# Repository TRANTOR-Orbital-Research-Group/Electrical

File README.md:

View this project on [CADLAB.io](https://cadlab.io/project/30550). 

# Electrical

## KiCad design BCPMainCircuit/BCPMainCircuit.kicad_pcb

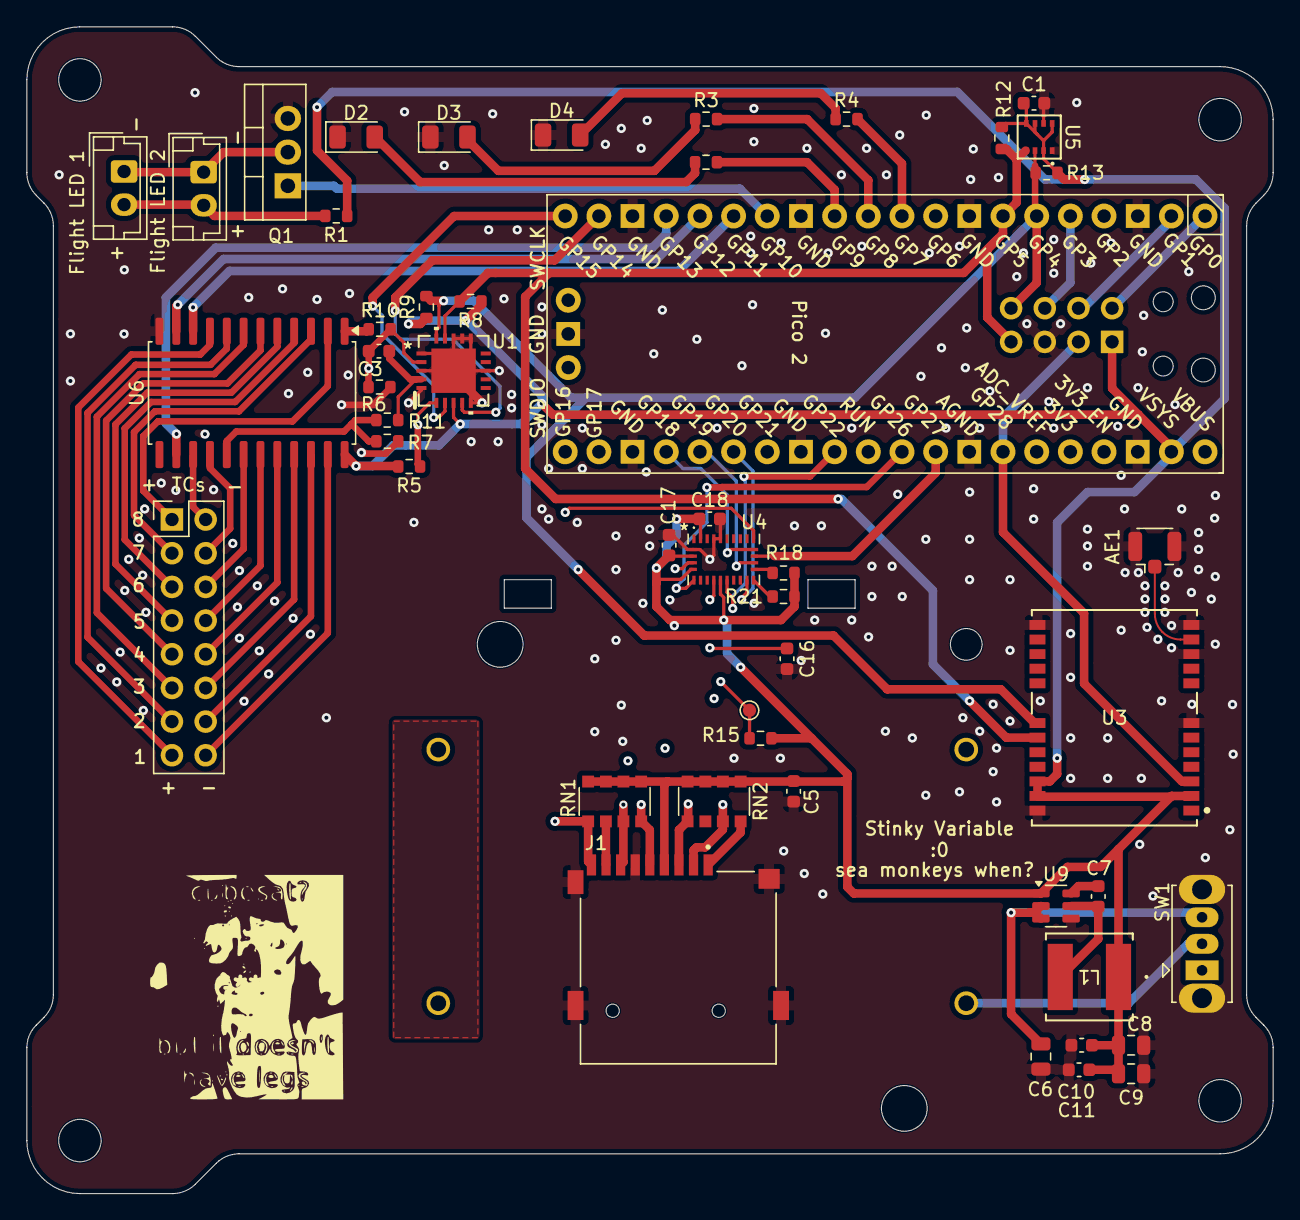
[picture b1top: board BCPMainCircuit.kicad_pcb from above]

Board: 4 copper layers, 94.0 x 88.0 mm, 49 parts (1 on the bottom side), 60 nets.

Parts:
AE1: Antenna_Shield; U.FL_Hirose_U.FL-R-SMT-1_Vertical
BT1: 1097P; BAT_1097P
C1: 220nf; C_0603_1608Metric
C3, C16, C17, C18: 0u1f; C_0603_1608Metric
C5, C11: 1uF; C_0603_1608Metric
C6: 10uF; C_0805_2012Metric
C7: 0u1F; C_0603_1608Metric
C8, C9: 22uF; C_0805_2012Metric
C10: 4u7F; C_0603_1608Metric
D1: Flight LED 1; JST_EH_B2B-EH-A_1x02_P2.50mm_Vertical
D2: DEBUG 1; LED_1206_3216Metric
D3: DEBUG 2; LED_1206_3216Metric
D4: BEBUG 3; LED_1206_3216Metric
D5: Flight LED 2; JST_EH_B2B-EH-A_1x02_P2.50mm_Vertical
J1: MSD-4-A; CUI_MSD-4-A
L1: 4u7H; IND_VLS6045EX-4R7M_TDK
Q1: IRLB8721PBF; TO-220-3_Vertical
R1: 20Ω; R_0603_1608Metric
R2, R3, R4: 65Ω; R_0603_1608Metric
R5: 1M; R_0603_1608Metric
R6, R7: 2M; R_0603_1608Metric
R8, R9: 10k; R_0603_1608Metric
R10, R11: 100; R_0603_1608Metric
R12, R13: 4.7kΩ; R_0603_1608Metric
R15: 10kΩ; R_0603_1608Metric
R18, R21: 4kΩ; R_0603_1608Metric
RN1, RN2: CAY16-4702F4LF; R_Array_Convex_4x1206
SW1: Switch; SW_Slide_SPDT_Straight_CK_OS102011MS2Q
TCs: PinHeader_2x08_P2.54mm_Vertical
U1: MCP9601T-E/MX; MQFN20_NU_MCH
U2: Pico 2; RPi_Pico_SMD_TH
U3: NEO-M9N-00B; SMT_9N-00B_UBL
U4: BNO085; IC_BNO085
U5: BME280; BME280(1)
U6: CD4097B; SOIC-24W_7.5x15.4mm_P1.27mm
U9: AP63203WU-7; TSOT-23-6

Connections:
+3.3V: C1.1, C5.1, C8.1, C9.1, C10.1, C11.1, C17.1, C18.1, J1.4 (VDD), L1.1, R1.1, R5.2, R8.1, R9.1, R12.1, R13.2, R15.1, R18.2, R21.2, RN1.1, RN1.2, RN1.3, RN1.4, RN2.1, RN2.2, RN2.3, RN2.4, U1.8 (VDD), U2.39 (VSYS), U3.2 (D_SEL), U3.22 (V_BCKP), U3.23 (VCC), U4.3 (VDD), U4.5 (PS1), U4.10 (CLKSEL0), U4.28 (VDDIO), U5.2 (CSB), U5.5 (SDO), U5.6 (VDDIO), U5.8 (VDD), U6.24 (VDD), U9.1 (FB)
BATT+: C6.1, SW1.3 (A), U9.2 (EN), U9.3 (VIN)
DEBUG1: R2.2, U2.12 (GPIO9)
DEBUG2: R3.2, U2.11 (GPIO8)
DEBUG3: R4.2, U2.10 (GPIO7)
FLIGHTLED: Q1.1 (G), U2.14 (GPIO10)
GND: AE1.2 (Shield), BT1.N2, C1.2, C5.2, C6.2, C8.2, C9.2, C10.2, C11.2, C16.2, C17.2, C18.2, D2.1 (K), D3.1 (K), D4.1 (K), J1.6 (VSS), J1.G1 (COVER_GND), J1.G2 (COVER_GND__1), J1.G3 (COVER_GND__2), J1.G4 (COVER_GND__3), Q1.3 (S), R6.1, R7.2, U1.1 (GND), U1.3 (GND), U1.5 (GND), U1.10 (GND), U1.13 (GND), U1.16 (ADDR), U1.17 (GND), U1.18 (GND), U1.21 (GND), U2.3 (GND), U2.8 (GND), U2.13 (GND), U2.18 (GND), U2.23 (GND), U2.28 (GND), U2.33 (AGND), U2.38 (GND), U2.42 (GND), U3.7 (V_USB), U3.10 (GND), U3.12 (GND), U3.13 (GND), U3.24 (GND), U4.2 (GND), U4.25 (GNDIO), U4.26 (XOUT32/CLKSEL1), U5.1 (GND), U5.7 (GND), U6.12 (VSS), U9.4 (GND)
IMU_Boot: R15.2, U4.4 (~BOOT)
IMU_CS: U2.32 (GPIO27_ADC1), U4.18 (~H_CS)
IMU_Int: U2.26 (GPIO20), U4.14 (~H_INT)
IMU_RST: U2.29 (GPIO22), U4.11 (~RST)
IMU_Wake: U2.31 (GPIO26_ADC0), U4.6 (PS0/WAKE)
unnamed: AE1.1 (A), U3.11 (RF_IN)
unnamed: BT1.N1, BT1.P2
unnamed: D1.2 (A), D5.2 (A), R1.2
unnamed: D1.1 (K), D5.1 (K), Q1.2 (D)
unnamed: D2.2 (A), R2.1
unnamed: D3.2 (A), R3.1
unnamed: D4.2 (A), R4.1
unnamed: J1.8 (DAT1), RN1.6
unnamed: J1.1 (DAT2), RN2.8
unnamed: BT1.P1, SW1.2 (B)
unnamed: C3.2, R11.2, U1.4 (VIN-)
unnamed: C16.1, U4.9 (CAP)
unnamed: R21.1, U4.15 (ENV_SCL)
unnamed: R18.1, U4.16 (ENV_SDA)
unnamed: C7.1, U9.6 (BST)
unnamed: C7.2, L1.2, U9.5 (SW)
SCL: R8.2, R12.2, U1.19 (SCL), U2.7 (GPIO5), U3.19 (SCL_/_SPI_SLK), U5.4 (SCK)
SDA: R9.2, R13.1, U1.20 (SDA), U2.6 (GPIO4), U3.18 (SDA_/_SPI_CS_N), U5.3 (SDI)
SD_CD: J1.CD, RN1.5, U2.27 (GPIO21)
SD_CS: J1.2 (CD/DAT3), RN2.7, U2.22 (GPIO17)
SD_MISO: J1.7 (DAT0), RN1.7, U2.21 (GPIO16), U4.20 (H_SDA/H_MISO/TX)
SD_MOSI: J1.3 (CMD), RN2.5, U2.25 (GPIO19), U4.17 (SA0/H_MOSI)
SD_SCK: J1.5 (CLK), RN1.8, U2.24 (GPIO18), U4.19 (H_SCL/SCK/RX)
TC+1: TCs.15, U6.9 (X0)
TC+2: TCs.13, U6.8 (X1)
TC+3: TCs.11, U6.7 (X2)
TC+4: TCs.9, U6.6 (X3)
TC+5: TCs.7, U6.5 (X4)
TC+6: TCs.5, U6.4 (X5)
TC+7: TCs.3, U6.3 (X6)
TC+8: TCs.1, U6.2 (X7)
TC+YLW: R10.1, U6.1 (X)
TC-1: TCs.16, U6.23 (Y0)
TC-2: TCs.14, U6.22 (Y1)
TC-3: TCs.12, U6.21 (Y2)
TC-4: TCs.10, U6.20 (Y3)
TC-5: TCs.8, U6.19 (Y4)
TC-6: TCs.6, U6.18 (Y5)
TC-7: TCs.4, U6.16 (Y6)
TC-8: TCs.2, U6.15 (Y7)
TC-RED: R7.1, R11.1, U6.17 (Y)
TC-Sel1: U2.15 (GPIO11), U6.10 (A)
TC-Sel2: U2.16 (GPIO12), U6.11 (B)
TC-Sel3: U2.17 (GPIO13), U6.14 (C)
ThermoOCwarn: U1.9 (OCALERT), U2.19 (GPIO14)
ThermoSCwarn: U1.7 (SCALERT), U2.20 (GPIO15)
TimePulseGPS: U2.34 (GPIO28_ADC2), U3.3 (TIMEPULSE)
VSense1: C3.1, R5.1, R6.2, R10.2, U1.2 (VIN+), U1.6 (VSENSE)

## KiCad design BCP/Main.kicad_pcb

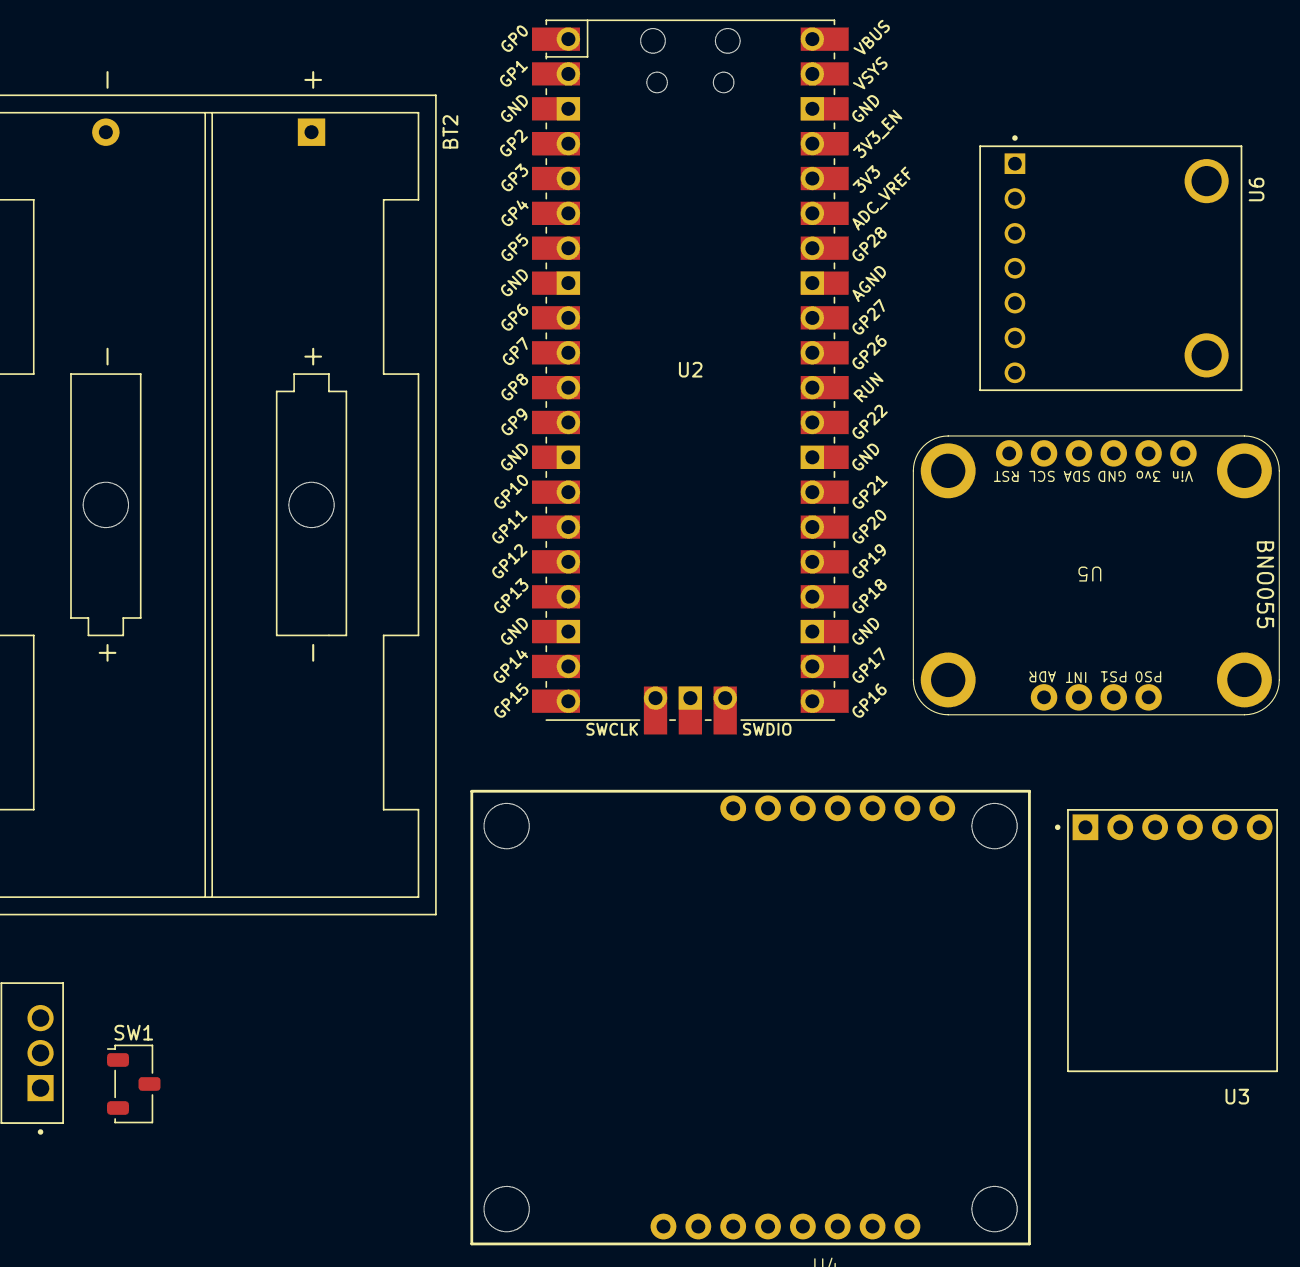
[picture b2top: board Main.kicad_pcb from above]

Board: 2 copper layers, 8 parts (0 on the bottom side), 8 nets.

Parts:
BT2: Battery; BatteryHolder_Keystone_2462_2xAA
SW1: SW_Nidec_CAS-120A1; Nidec_Copal_CAS-120A
U1: LD1117V33; TO255P1020X450X1968-3
U2: Pico 2; RPi_Pico_SMD_TH
U3: DEV-13712; MODULE_DEV-13712
U4: GPS
U5: BNO055
U6: BME280

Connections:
/3.3 V: U1.2 (VOUT), U3.3 (VCC), U4.11 (3V3), U5.1 (VIN), U6.1 (VIN)
/MCURX: U2.2 (GPIO1), U3.4 (TXO)
/MCUTX: U2.1 (GPIO0), U3.5 (RXI)
/SCL: U2.7 (GPIO5), U4.8 (SCL), U5.5 (SCL), U6.4 (SCK)
/SDA: U2.6 (GPIO4), U4.7 (SDA), U5.4 (SDA), U6.5 (SDO)
GND: U1.1 (ADJ/GND), U2.3 (GND), U2.38 (GND), U3.2 (GND), U3.6 (GRN), U4.5 (GND), U4.9 (GND), U5.3 (GND), U6.3 (GND)
unnamed: BT2.1 (+), SW1.2 (B)
unnamed: SW1.3 (A), U1.3 (VIN)

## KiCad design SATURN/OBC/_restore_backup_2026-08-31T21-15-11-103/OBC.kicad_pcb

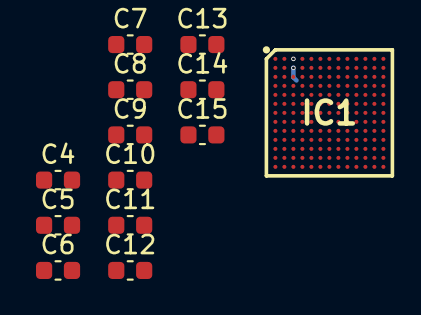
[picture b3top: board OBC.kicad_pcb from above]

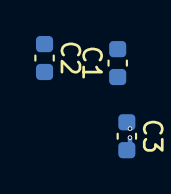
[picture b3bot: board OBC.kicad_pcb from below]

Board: 6 copper layers, 16 parts (3 on the bottom side), 4 nets.

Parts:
C1, C2: 2.2uf; C_0603_1608Metric
C3, C4, C5, C6, C7, C8, C9, C10, C11, C12, C13, C14, C15: 100nf?; C_0603_1608Metric
IC1: STM32H735AGI6; BGA169C50P13X13_700X700X60

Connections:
MCU_VDD: C3.1, C4.1, C5.1, C6.1, C7.1, C8.1, C9.1, C10.1, C11.1, C12.1, C13.1, C14.1, C15.1, IC1.A3 (VDD_1), IC1.A6 (VDD_2), IC1.A7 (VDD_3), IC1.C13 (VDD_5), IC1.D1 (VDD_6), IC1.G1 (VDD_7), IC1.H13 (VDD_8), IC1.L13 (VDD_9), IC1.M1 (VDD_10), IC1.N4 (VDD_11), IC1.N7 (VDD_12), IC1.N11 (VDD_13)
MCU_VSS: C1.1, C2.1, C3.2, C4.2, C5.2, C6.2, C7.2, C8.2, C9.2, C10.2, C11.2, C12.2, C13.2, C14.2, C15.2, IC1.B3 (VSS_1), IC1.B7 (VSS_2), IC1.B10 (VSS_3), IC1.C12 (VSS_4), IC1.D2 (VSS_5), IC1.G2 (VSS_6), IC1.H12 (VSS_7), IC1.L12 (VSS_8), IC1.M2 (VSS_9), IC1.M4 (VSS_10), IC1.M7 (VSS_11), IC1.M11 (VSS_12)
unnamed: C1.2, IC1.A4 (VCAP_1)
unnamed: C2.2, IC1.D13 (VCAP_2)

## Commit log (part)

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2025-11-01 Initial Push
2025-11-01 Rename
2025-11-01 Added GPS (somewhat)
2025-11-01 Added an Autosave
2025-11-01 Removed autosave (I swear I know what I'm doing)
2025-11-02 Added GPS and BME
2025-11-02 Theoretically done?
2025-11-02 Grouped Like Components
2025-11-02 Minor Changes
2025-11-02 Added silkscreen updates
2025-11-03 Update cutout
2025-11-03 Silkscreen Fixes
2025-11-03 Added library for symbols (currently empty, but seems like good practice for future)
2025-11-03 Traces Run for V1
2025-11-03 Powering the pico, whoops
2025-11-04 Thickening power traces
2025-11-04 Added a ground pour
2025-11-04 Fixed overlapping footprints
2025-11-05 Update LEDs and Silkscreen
2025-11-06 Update PCB design
    Added four new backup ZIP files for BCPMainCircuit. Updated the KiCad PCB file to include a detailed stackup and new F.SilkS graphics, and made related changes to the .kicad_prl and fp-info-cache fil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
2025-11-08 added text
2025-11-08 added text
    :)
2025-11-09 Major changes: Redid traces to be thicker Moved Pico to back and rotated 180 Added resistors for LEDs (no values yet) Changed pins for flight led (i think) Changed BME280 footprint to the one we have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
    Minor changes:
    Added caps to v.reg
    Rearranged some components (freed up a good bit of space!)
    Changed PMOS to NMOS
    Edited footprints to better reflect actual parts/needs (assuming most parts are the same as two-month parts)
    other stuff idk
2025-11-10 Major changes: Added 2x 8:1 multiplexers for thermocouples, up to 8, can be selected using pins 19,20,21 IN REVERSE ORDER! Added 1 primary TC amp, with capacity for 2 extra using ADC 0,1,2 Moved flig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
    Minor changes:
    Flight leds share a resistor now since they use constant current
    moved some stuff i think
    Debug leds moved to 7,8,9 IN REVERSE ORDER!
    other stuff?
2025-11-15 Major changes: Removed TC amps, replaced with SMD TC amps instead idk
2025-11-15 Added datasheet links
2025-11-16 minor changes n stuff
2025-11-18 minor stuff working on SD card thing and tc amp and power Next steps: SMD components!!!
2025-11-19 lsm6dso
2025-11-25 minor changes (everything is being redone using smd components instead of breakout boards) still need : gps antenna + schematic (capacitors?) IMU (current one needs 1.8v!!!!!!!!!!!!!!!!) RGB LEDs? 16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
2025-11-26 in the middle of stuff NOTES: replace 2xmux with 1x cheaper mux? RGB leds HOW? how to sd card? magnetometer trade check stock of resistors, capacitors, inductors, sd slots, etc etc
2025-11-27 finished magnetometer and imu still need: GPS stuff SD card stuff RGB LEDs
2025-12-03 Replaced mux with different, smaller, smd, cheaper one put flight leds back
    NEED TO DO:
    add gps antenna
    check if gps needs filter caps
    verify v. reg capacitors (size, footprint, values)
    figure out how sd cards work (im confused by them, for i have a simple mind)
    breakout pins for everything we'd want
2025-12-04 added gps antenna sd card is hopefully correct breakout pins added ran drc, only mad about the 0603 sized stuff having insufficient clearance, probably fine
    still need someone to verify:
    v. reg capacitors n stuff
    gps filter caps???
    every smd thing lol, its SO BAD
    and
    software needs to review available breakout pins, as well as other misc. stuff to be sure its good
2025-12-06 fixed stuff
2025-12-07 changed imu
2026-01-05 changed the battery holder size, hope it's not too close to the edge
2026-01-12 cleanup
2026-01-14 More cleanup
2026-01-24 minor cleanup
2026-02-02 Working on STUFF(tm)
2026-02-03 Messy but working on turing it into a hierarchical schematic
2026-06-22 BCP Board Revision V.01
2026-06-29 Added 2 layers, and connected data lines
2026-06-29 Create OBC.ioc
    aaaaa
